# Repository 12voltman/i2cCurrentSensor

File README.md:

# i2cCurrentSensor
Low voltage current sensor with onboard micro to simplify AC measurements

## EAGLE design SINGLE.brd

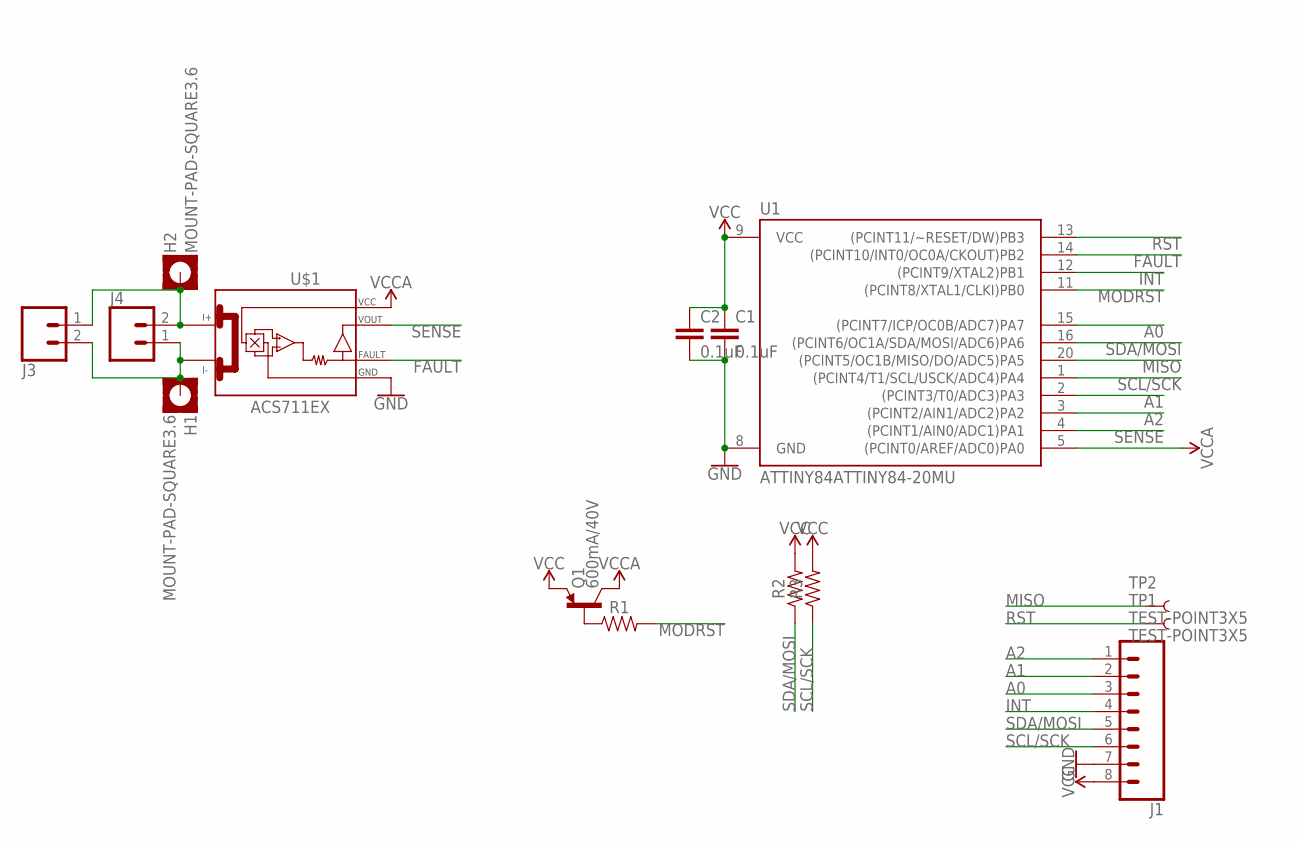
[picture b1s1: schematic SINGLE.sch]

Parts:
C1, C2: 0.1uF; 0603
H1, H2: MOUNT-PAD-SQUARE3.6; 3,6-PAD-SQUARE
J1: CONN_08NO_SILK_FEMALE_PTH; 1X08_NO_SILK
J3: CONN_025MM; SCREWTERMINAL-5MM-2
J4: CONN_02; 1X02
Q1: 600mA/40V; SOT23-3
R1, R2, R3: 0603
TP1, TP2: TEST-POINT3X5; PAD.03X.05
U1: ATTINY84ATTINY84-20MU; QFN20
U$1: ACS711EX; QFN-12EX_3X3

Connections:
A0: J1.3, U1.15 ((PCINT7/ICP/OC0B/ADC7)PA7)
A1: J1.2, U1.2 ((PCINT3/T0/ADC3)PA3)
A2: J1.1, U1.3 ((PCINT2/AIN1/ADC2)PA2)
FAULT: U1.14 ((PCINT10/INT0/OC0A/CKOUT)PB2), U$1.P$4 (FAULT)
GND: C1.2, C2.2, J1.7, U1.8 (GND), U$1.P$3 (GND)
INT: J1.4, U1.12 ((PCINT9/XTAL2)PB1)
MISO: TP2.P$1, U1.20 ((PCINT5/OC1B/MISO/DO/ADC5)PA5)
MODRST: R1.2, U1.11 ((PCINT8/XTAL1/CLKI)PB0)
unnamed: H1.B3,6, J3.2, J4.1, U$1.P$2 (I-_1)
unnamed: H2.B3,6, J3.1, J4.2, U$1.P$1 (I+_1)
unnamed: Q1.1 (B), R1.1
RST: TP1.P$1, U1.13 ((PCINT11/~RESET/DW)PB3)
SCL/SCK: J1.6, R3.1, U1.1 ((PCINT4/T1/SCL/USCK/ADC4)PA4)
SDA/MOSI: J1.5, R2.1, U1.16 ((PCINT6/OC1A/SDA/MOSI/ADC6)PA6)
SENSE: U1.4 ((PCINT1/AIN0/ADC1)PA1), U$1.P$9 (VOUT)
VCC: C1.1, C2.1, J1.8, Q1.2 (E), R2.2, R3.2, U1.9 (VCC)
VCCA: Q1.3 (C), U1.5 ((PCINT0/AREF/ADC0)PA0), U$1.P$10 (VCC)

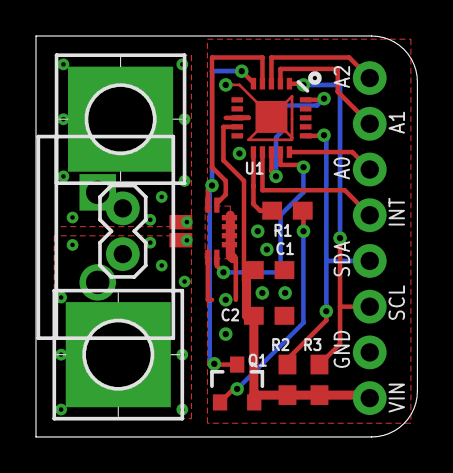
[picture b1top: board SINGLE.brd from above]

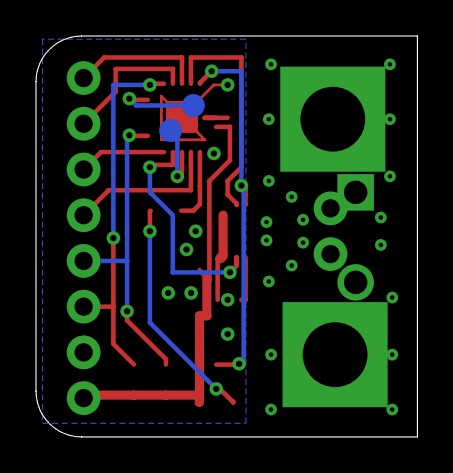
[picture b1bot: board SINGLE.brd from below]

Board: 2 copper layers, 21.2 x 22.3 mm, 15 parts (2 on the bottom side), 17 nets.

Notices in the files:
parts and their libraries:
SparkFun-Connectors: Licensing: Creative Commons ShareAlike 4.0 International - https://creativecommons.org/licenses/by-sa/4.0
